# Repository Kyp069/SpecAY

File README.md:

# SpecAY

An AY-3-8912 sound interface for the ZX Spectrum 48K.
Compatible with Spectrum 128K ports.
Designed with KiCAD.

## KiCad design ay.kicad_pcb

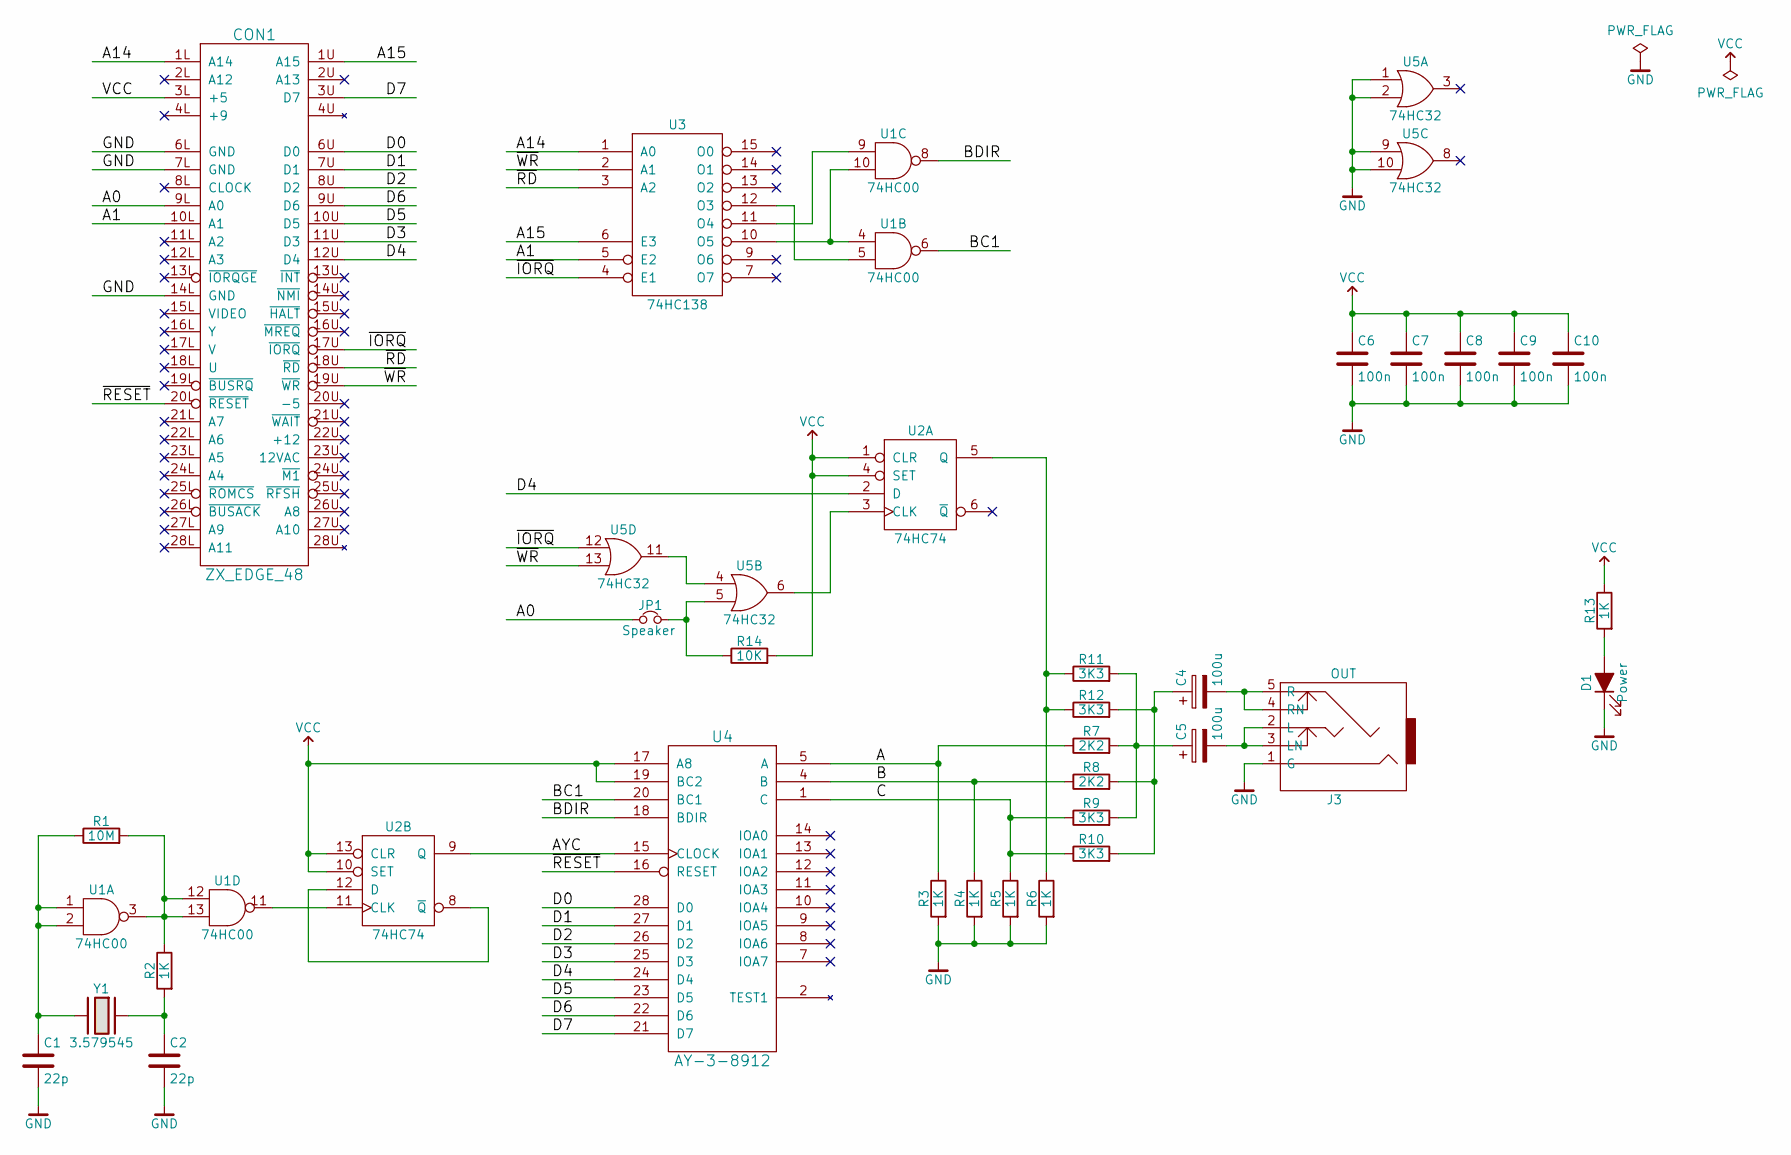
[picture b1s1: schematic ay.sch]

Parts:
C1, C2: 22p; C_Disc_D4.3mm_W1.9mm_P5.00mm
C4, C5: 100u; CP_Radial_D5.0mm_P2.50mm
C6, C7, C8, C9, C10: 100n; C_Disc_D4.3mm_W1.9mm_P5.00mm
CON1: ZX_EDGE_48; BUS
D1: Power; LED_D3.0mm
J3: OUT; 3.5mm_Jack
JP1: Speaker; Pin_Header_Straight_1x02_Pitch2.54mm
R1: 10M; R_Axial_DIN0204_L3.6mm_D1.6mm_P7.62mm_Horizontal
R2, R3, R4, R5, R6, R13: 1K; R_Axial_DIN0204_L3.6mm_D1.6mm_P7.62mm_Horizontal
R7, R8: 2K2; R_Axial_DIN0204_L3.6mm_D1.6mm_P7.62mm_Horizontal
R9, R10, R11, R12: 3K3; R_Axial_DIN0204_L3.6mm_D1.6mm_P7.62mm_Horizontal
R14: 10K; R_Axial_DIN0204_L3.6mm_D1.6mm_P7.62mm_Horizontal
U1: 74HC00; DIP-14_W7.62mm_Socket
U2: 74HC74; DIP-14_W7.62mm_Socket
U3: 74HC138; DIP-16_W7.62mm_Socket
U4: AY-3-8912; DIP-28_W15.24mm_Socket
U5: 74HC32; DIP-14_W7.62mm_Socket
Y1: 3.579545; Crystal_HC49-U_Vertical

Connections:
/A: R3.1, R7.1, U4.5 (A)
/A0: CON1.9L (A0), JP1.2; also elsewhere on the board
/A1: CON1.10L (A1), U3.5 (E2)
/A14: CON1.1L (A14), U3.1 (A0)
/A15: CON1.1U (A15), U3.6 (E3)
/AYC: U2.9 (Q), U4.15 (CLOCK)
/B: R4.1, R8.1, U4.4 (B)
/BC1: U1.6, U4.20 (BC1)
/BDIR: U1.8, U4.18 (BDIR)
/C: R5.1, R9.1, R10.1, U4.1 (C)
/D0: CON1.6U (D0), U4.28 (D0)
/D1: CON1.7U (D1), U4.27 (D1)
/D2: CON1.8U (D2), U4.26 (D2)
/D3: CON1.11U (D3), U4.25 (D3)
/D4: CON1.12U (D4), U2.2 (D), U4.24 (D4)
/D5: CON1.10U (D5), U4.23 (D5)
/D6: CON1.9U (D6), U4.22 (D6)
/D7: CON1.3U (D7), U4.21 (D7)
/~IORQ: CON1.17U (~IORQ), U3.4 (E1), U5.12
/~RD: CON1.18U (~RD), U3.3 (A2)
/~RESET: CON1.20L (~RESET), U4.16 (RESET)
/~WR: CON1.19U (~WR), U3.2 (A1), U5.13
GND: C1.2, C2.2, C6.2, C7.2, C8.2, C9.2, C10.2, CON1.6L (GND), CON1.7L (GND), CON1.14L (GND), D1.1 (K), J3.1 (G), R3.2, R4.2, R5.2, R6.2, U1.7 (GND), U2.7 (GND), U3.8 (GND), U4.6 (GND), U5.1, U5.2, U5.7 (GND), U5.9, U5.10; also elsewhere on the board
unnamed: C1.1, R1.1, U1.1, U1.2, Y1.2
unnamed: C2.1, R2.2, Y1.1
unnamed: C4.1, R8.2, R10.2, R12.2
unnamed 26: C4.2, J3.4 (RN), J3.5 (R); also elsewhere on the board
unnamed: C5.1, R7.2, R9.2, R11.2
unnamed 28: C5.2, J3.2 (L), J3.3 (LN); also elsewhere on the board
unnamed 29: D1.2 (A), R13.2; also elsewhere on the board
unnamed 30: JP1.1, R14.1, U5.5; also elsewhere on the board
unnamed: R1.2, R2.1, U1.3, U1.12, U1.13
unnamed: R6.1, R11.1, R12.1, U2.5 (Q)
unnamed: U1.5, U3.12 (O3)
unnamed: U1.9, U3.11 (O4)
unnamed: U1.4, U1.10, U3.10 (O5)
unnamed: U1.11, U2.11 (CLK)
unnamed: U2.3 (CLK), U5.6
unnamed: U2.8 (~Q), U2.12 (D)
unnamed: U5.4, U5.11
VCC: C6.1, C7.1, C8.1, C9.1, C10.1, CON1.3L (+5), R13.1, R14.2, U1.14 (VCC), U2.1 (CLR), U2.4 (SET), U2.10 (SET), U2.13 (CLR), U2.14 (VCC), U3.16 (VCC), U4.3 (VCC), U4.17 (A8), U4.19 (BC2), U5.14 (VCC)

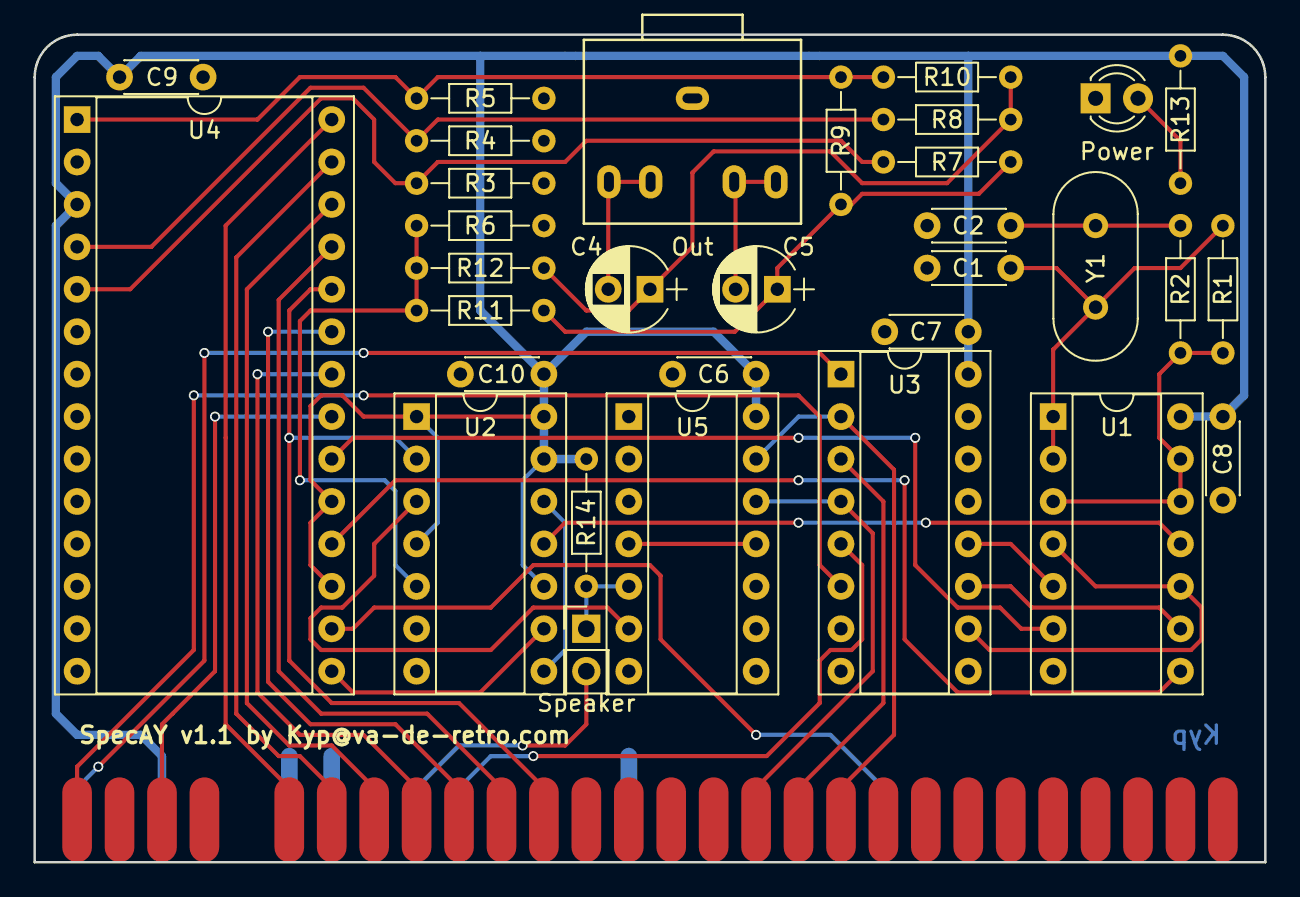
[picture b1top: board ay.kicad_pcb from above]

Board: 2 copper layers, 73.7 x 49.5 mm, 33 parts (0 on the bottom side), 41 nets.

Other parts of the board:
Out: OUT; 3.5mm_Jack
Power: Power; LED_D3.0mm
Speaker: Speaker; Pin_Header_Straight_1x02_Pitch2.54mm

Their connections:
/A0: Speaker.2; also elsewhere on the board
GND: Out.1, Power.1; also elsewhere on the board
unnamed 26: Out.4, Out.5; also elsewhere on the board
unnamed 28: Out.2, Out.3; also elsewhere on the board
unnamed 29: Power.2; also elsewhere on the board
unnamed 30: Speaker.1; also elsewhere on the board

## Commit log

2021-02-01 Added BOM
